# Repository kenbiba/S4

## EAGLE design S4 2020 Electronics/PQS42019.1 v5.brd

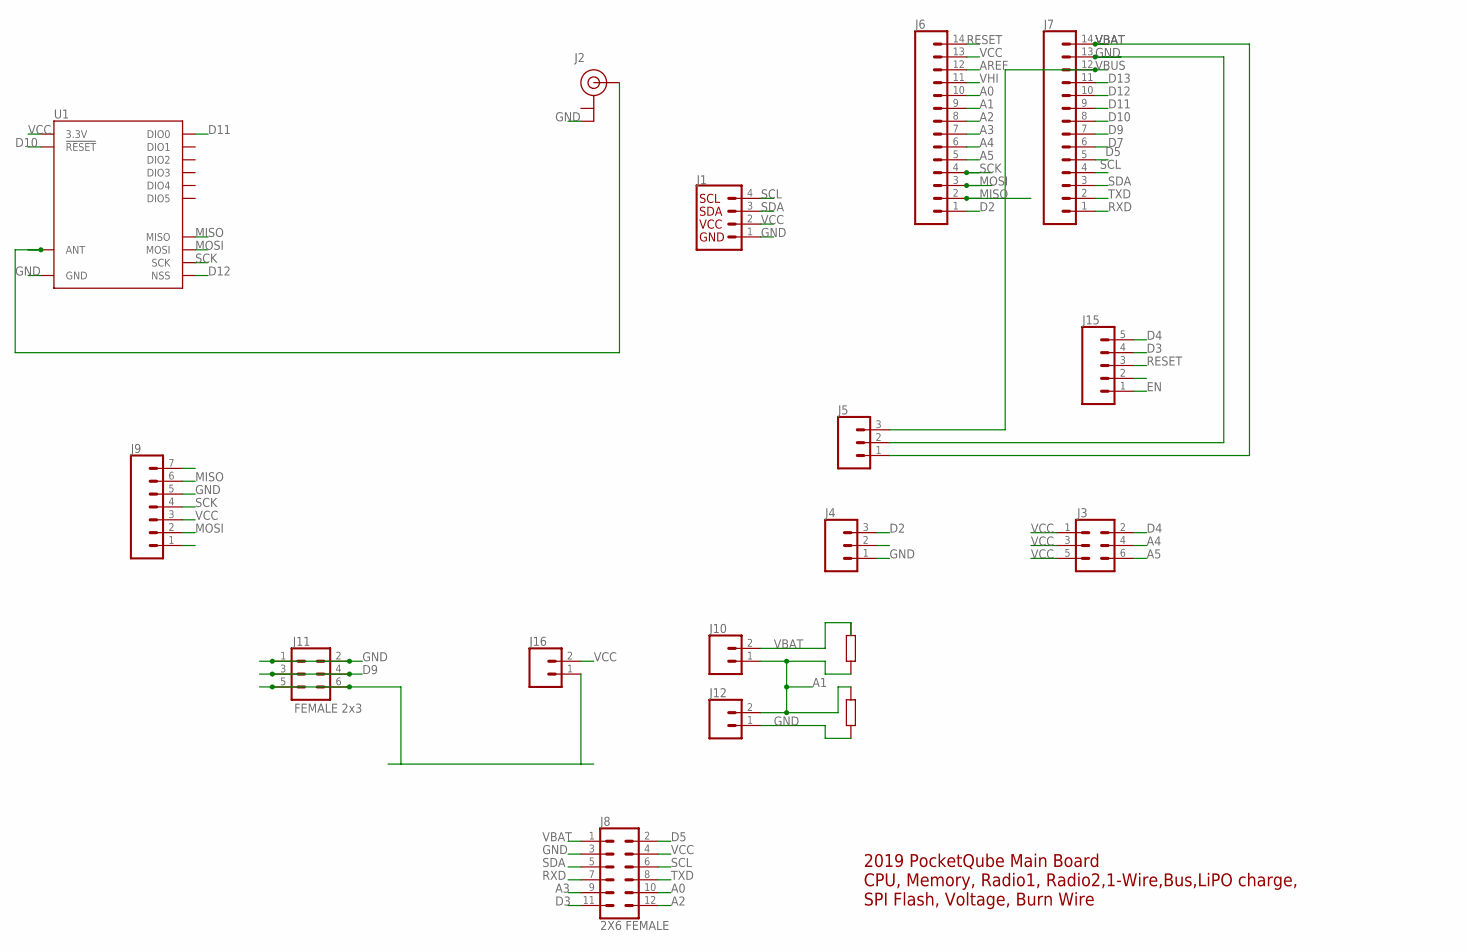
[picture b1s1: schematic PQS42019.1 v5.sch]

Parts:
J1: QWIIC_CONNECTORJS-1MM; 1X04_1MM_RA
J2: U.FL
J3: CONN_03X2NO_SILK; 2X3-NS
J4, J5: CONN_03; 1X03
J6, J7: CONN_14; 1X14
J8: 2X6 FEMALE; 2X6
J9: CONN_07; 1X07
J10, J12, J16: CONN_02; 1X02
J11: FEMALE 2x3; 2X3
J15: CONN_05; 1X05
U1: RFM95W; RFM95/96/97/98W

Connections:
A0: J6.10, J8.10
A1: J6.9, J10.1, J12.2
A2: J6.8, J8.12
A3: J6.7, J8.9
A4: J3.4, J6.6
A5: J3.6, J6.5
AREF: J6.12
D2: J4.3, J6.1
D3: J8.11, J15.4
D4: J3.2, J15.5
D5: J7.5, J8.2
D7: J7.6, J9.1
D9: J7.7, J11.3, J11.4
D10: J7.8, U1.!RESET
D11: J7.9, U1.DIO0
D12: J7.10, U1.NSS
D13: J7.11
EN: J15.1
GND: J1.1 (GND), J2.2 (GND), J4.1, J5.2, J7.13, J8.3, J9.5, J11.1, J11.2, J12.1, U1.GND@1 (GND), U1.GND@2 (GND), U1.GND@3 (GND)
MISO: J6.2, J9.6, U1.MISO
MOSI: J6.3, J9.2, U1.MOSI
unnamed: J11.5, J11.6, J16.1
unnamed: J2.FEED (SIGNAL), U1.ANT
RESET: J6.14, J15.3
RXD: J7.1, J8.7
SCK: J6.4, J9.4, U1.SCK
SCL: J1.4 (SCL), J7.4, J8.6
SDA: J1.3 (SDA), J7.3, J8.5
TXD: J7.2, J8.8
VBAT: J5.1, J7.14, J8.1, J10.2
VBUS: J5.3, J7.12
VCC: J1.2 (VCC), J3.1, J3.3, J3.5, J6.13, J8.4, J9.3, J16.2, U1.3.3V
VHI: J6.11

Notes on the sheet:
2019 PocketQube Main Board CPU, Memory, Radio1, Radio2,1-Wire,Bus,LiPO charge, SPI Flash, Voltage, Burn Wire

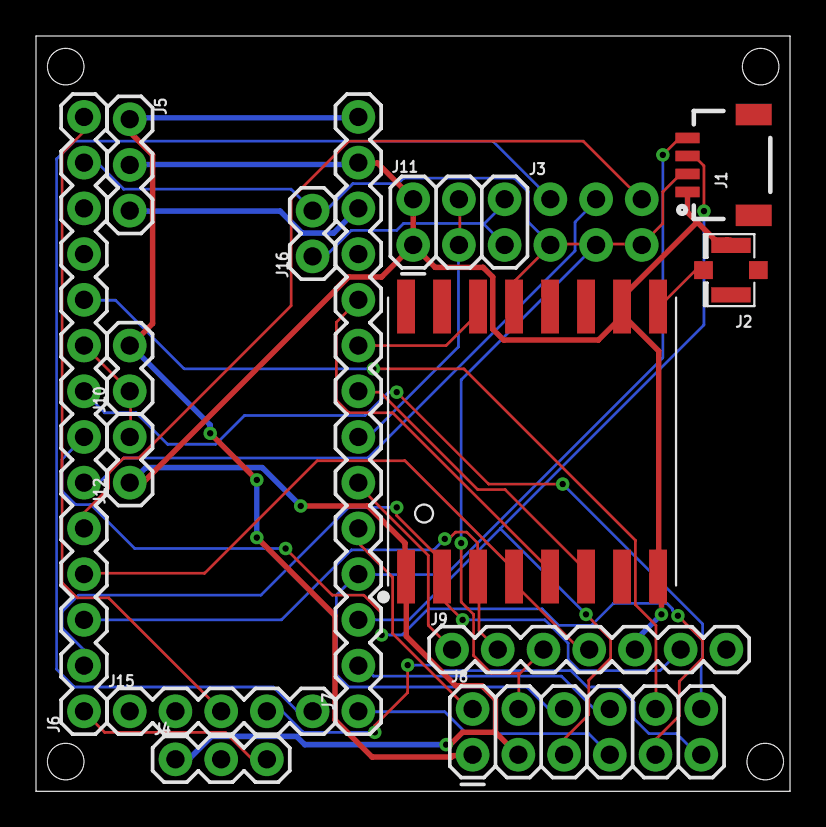
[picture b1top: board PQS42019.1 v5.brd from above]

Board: 2 copper layers, 41.9 x 42.0 mm, 15 parts (0 on the bottom side), 29 nets.

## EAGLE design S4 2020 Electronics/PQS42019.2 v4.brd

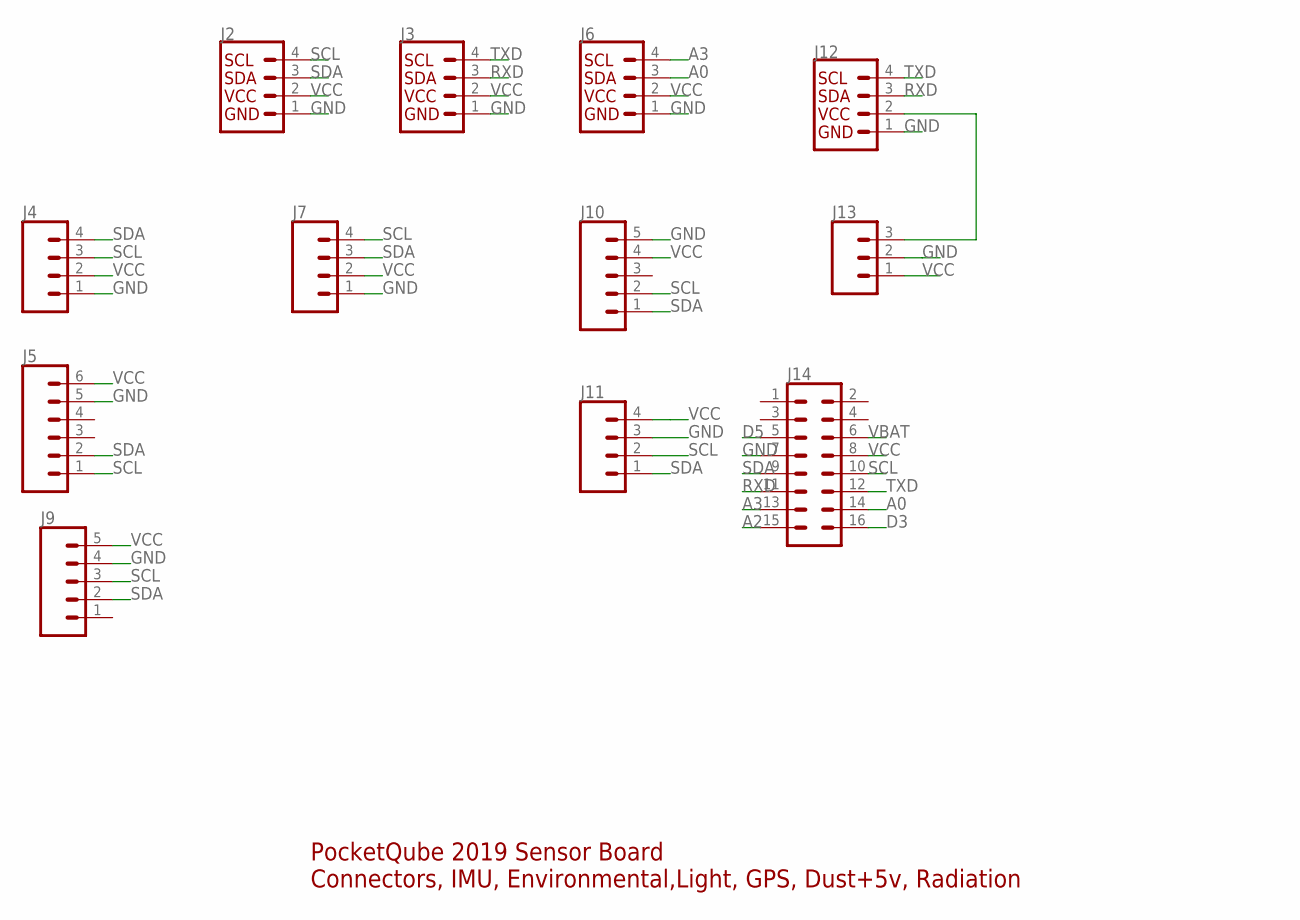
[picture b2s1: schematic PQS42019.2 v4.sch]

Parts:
J2, J3, J6, J12: QWIIC_CONNECTORJS-1MM; 1X04_1MM_RA
J4, J7, J11: CONN_04; 1X04
J5: CONN_06SILK_FEMALE_PTH; 1X06
J9, J10: CONN_05; 1X05
J13: CONN_03; 1X03
J14: CONN_08X2; 2X8

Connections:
A0: J6.3, J14.14
A2: J14.15
A3: J6.4, J14.13
D3: J14.16
D5: J14.5
GND: J2.1, J3.1, J4.1, J5.5, J6.1, J7.1, J9.4, J10.5, J11.3, J12.1, J13.2, J14.7
unnamed: J12.2, J13.3
RXD: J3.3, J12.3, J14.11
SCL: J2.4, J4.3, J5.1, J7.4, J9.3, J10.2, J11.2, J14.10
SDA: J2.3, J4.4, J5.2, J7.3, J9.2, J10.1, J11.1, J14.9
TXD: J3.4, J12.4, J14.12
VBAT: J14.6
VCC: J2.2, J3.2, J4.2, J5.6, J6.2, J7.2, J9.5, J10.4, J11.4, J13.1, J14.8

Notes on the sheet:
PocketQube 2019 Sensor Board Connectors, IMU, Environmental,Light, GPS, Dust+5v, Radiation

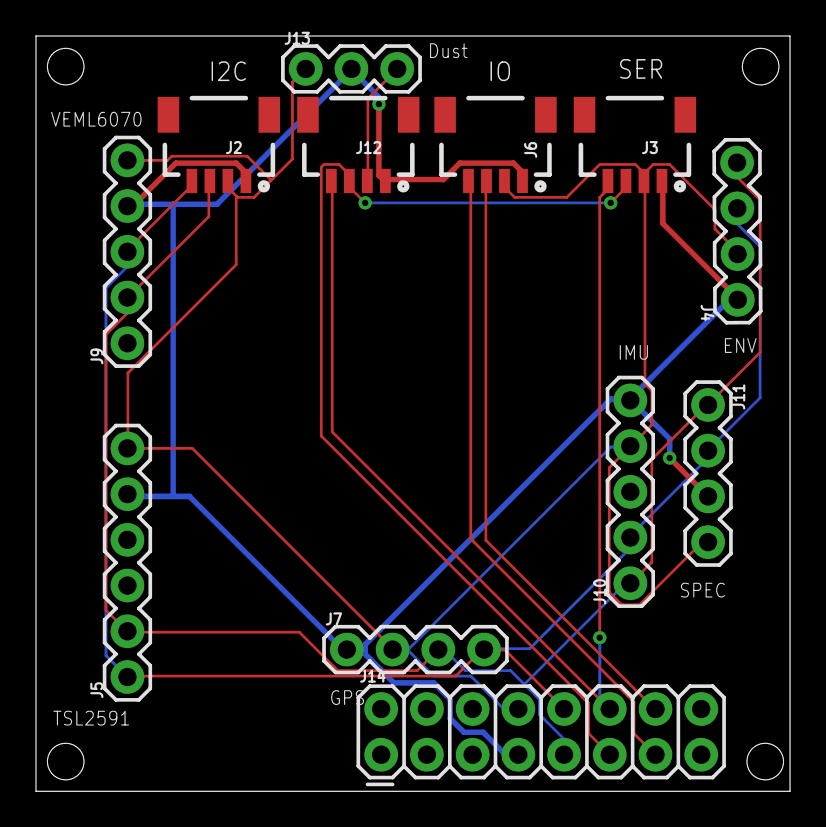
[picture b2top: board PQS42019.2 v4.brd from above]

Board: 2 copper layers, 41.9 x 42.0 mm, 12 parts (0 on the bottom side), 9 nets.

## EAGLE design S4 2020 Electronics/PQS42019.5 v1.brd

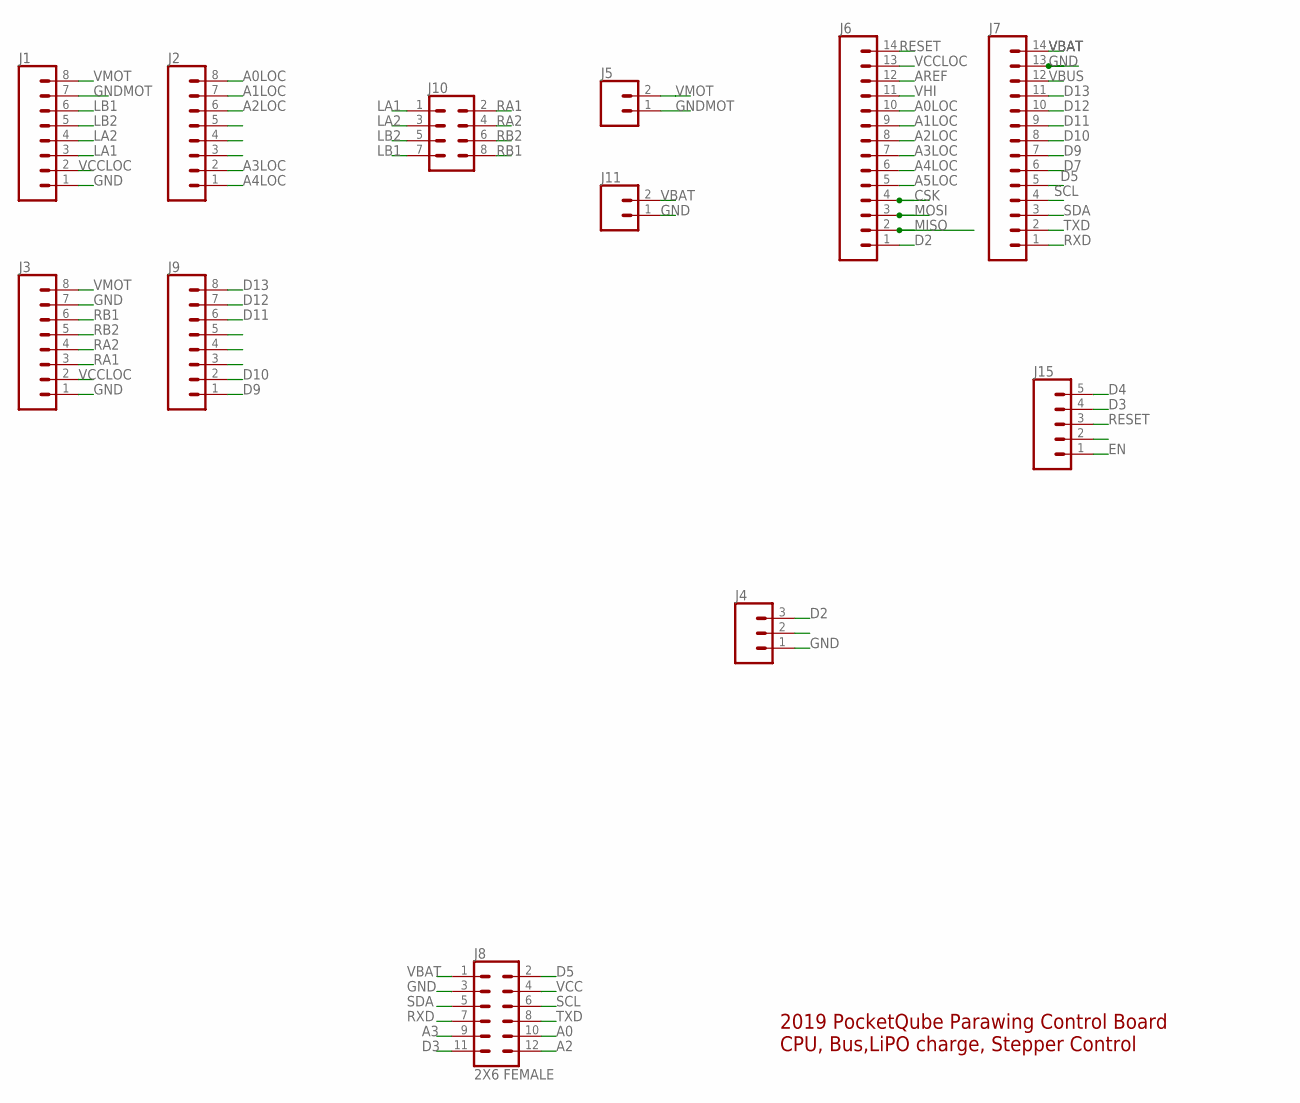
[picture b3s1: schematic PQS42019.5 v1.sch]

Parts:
J1, J2, J3, J9: CONN_08"; 1X08
J4: CONN_03; 1X03
J5, J11: CONN_02; 1X02
J6, J7: CONN_14; 1X14
J8: 2X6 FEMALE; 2X6
J10: CONN_04X2; 2X4
J15: CONN_05; 1X05

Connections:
A0: J8.10
A0LOC: J2.8, J6.10
A1LOC: J2.7, J6.9
A2: J8.12
A2LOC: J2.6, J6.8
A3: J8.9
A3LOC: J2.2, J6.7
A4LOC: J2.1, J6.6
A5LOC: J6.5
AREF: J6.12
CSK: J6.4
D2: J4.3, J6.1
D3: J8.11, J15.4
D4: J15.5
D5: J7.5, J8.2
D7: J7.6
D9: J7.7, J9.1
D10: J7.8, J9.2
D11: J7.9, J9.6
D12: J7.10, J9.7
D13: J7.11, J9.8
EN: J15.1
GND: J1.1, J3.1, J3.7, J4.1, J7.13, J8.3, J11.1
GNDMOT: J1.7, J5.1
LA1: J1.3, J10.1
LA2: J1.4, J10.3
LB1: J1.6, J10.7
LB2: J1.5, J10.5
MISO: J6.2
MOSI: J6.3
RA1: J3.3, J10.2
RA2: J3.4, J10.4
RB1: J3.6, J10.8
RB2: J3.5, J10.6
RESET: J6.14, J15.3
RXD: J7.1, J8.7
SCL: J7.4, J8.6
SDA: J7.3, J8.5
TXD: J7.2, J8.8
VBAT: J7.14, J8.1, J11.2
VBUS: J7.12
VCC: J8.4
VCCLOC: J1.2, J3.2, J6.13
VHI: J6.11
VMOT: J1.8, J3.8, J5.2

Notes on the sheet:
2019 PocketQube Parawing Control Board CPU, Bus,LiPO charge, Stepper Control

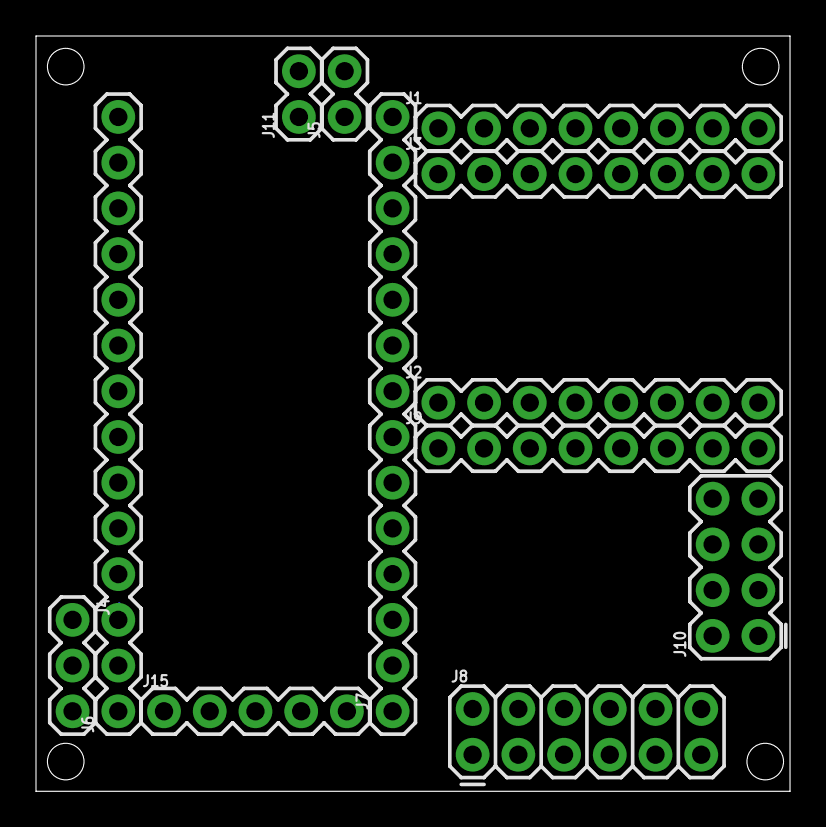
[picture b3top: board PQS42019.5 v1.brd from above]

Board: 2 copper layers, 41.9 x 42.0 mm, 12 parts (0 on the bottom side), 31 nets.

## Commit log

2020-05-25 New 2020 version of S4
2020-05-25 Baseline upload
    Baseline designs for package, elecronics and software for the 2020 S4
2020-05-25 Github references

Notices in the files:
parts and their libraries:
SparkFun-Connectors: Licensing: Creative Commons ShareAlike 4.0 International - https://creativecommons.org/licenses/by-sa/4.0
